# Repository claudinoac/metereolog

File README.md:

# 🌦️ Metereolog

This project involves the development of weather station and a platform capable of collecting data from various sensors, transmitting them to a central platform, storing them, and making them available through a web interface for visualization and analysis. The architecture is modular and scalable, using modern technologies for each stage of the process.

## 1. Project Overview

The main goal is to create a complete system for weather monitoring. This includes acquiring raw data from sensors, efficiently communicating this data to a central server, persistent storage in a time-series optimized database, and finally, visually and interactively presenting this data to users through a web application. Modularity allows for the easy addition of new sensors or replacement of components without affecting the whole system.

## 2. Project Architecture and Features

The architecture is distributed and based on microservices and asynchronous communication, as shown in the diagram. The main features include:

- **Distributed Data Collection:** Sensors are connected to embedded devices (HELTEC WiFi LoRa v3) that act as the network's "edge".
- **Local Gateways**: One local internet-connected dievice that aggregate data from stations in the region via LoRaWAN and transmit over the internet to the web platform via MQTT. 
- **Asynchronous, Message-Oriented Communication:** The MQTT protocol is used to transmit data from gateways to the message broker (RabbitMQ), ensuring low latency and resilience.
- **Centralized Message Processing:** RabbitMQ acts as a central hub for all sensor messages, enabling routing and processing by other components.
- **Optimized Data Persistence:** PostgreSQL and TimescaleDB provide a robust relational database optimized for time-series data.
- **RESTful API:** Facilitates communication between the frontend and backend, offering access to platform data and functionality.
- **Intuitive User Interface:** A modern, responsive web app allows for visualization and management of station data.
- **Containerization (Docker):** Simplifies deployment, portability, and environment management.
- **Modularity:** Each system component is independent, allowing isolated development and maintenance.

## 3. Modular Project Structure and Technologies Used

### 3.1. Data Acquisition Module (Hardware and Firmware)

- **Sensors:**
  - **DHT-11:** Measures temperature and humidity.
  - **Anemometer:** Measures wind speed.
  - **Wind Direction Sensor:** Measures wind direction.
  - **MQ-6:** Measures petroleum-based gas such as propane and butane

- **Heltec WiFi LoRa 32 v3 (Sensor Bus / Weather Station):**
  - Microcontroller responsible for reading sensor data.
  - Acts as the local station’s “brain”.
  - Transmit sensor data to the Gateway node via LoRaWAN
  - **Technologies:** PlatformIO (C++ SDK), LoRaWAN, WiFi.
  - **Features:**
    - Base libraries for each sensor and peripherals (DHT-11, Anemometer, Wind Direction, WiFi, LoRa, etc.).
    - Structured firmware codebase.
    - Local wifi network to view real-time sensors data.
    - Firmware update via OTA (WiFi).
    - Doesn't depend on internet (data transmission via LoRaWAN).

- **Heltec WiFi LoRa 32 v3 (Gateway):**
  - Microcontroller responsible for receiving data from stations via LoRaWAN
  - Publishes sensor data from stations to the MQTT broker.
  - Firmware update via OTA (WiFi).
  - MQTT integration for data transmission.
  - **Technologies:**: PlatformIO (C++ SDK), LoRaWAN, WiFi.
  - **Features:**
    - Base libraries for peripherals (WiFi, LoRa, etc.)
    - Can route data from multiple stations on LoRaWAN reach.
    - Routes data to MQTT broker based on each station specs (credentials, topics).
    - Structured firmware codebase.
    - Firmware update via OTA (WiFi).

### 3.2. Communication and Messaging Module

- **RabbitMQ + MQTT Plugin:**
  - Central message broker for the system.
  - Receives MQTT messages from ESP-32.
  - Forwards them to subscribed components.
  - **Features:**
    - Reliable message delivery.
    - Decoupling producers and consumers.
    - Scalability.
  - **Topic Notation:**  
    - `<device_uid>/<sensor_uid>` = MQTT topics  
    - `mqtt.*` = wildcard listener  
    - `sensors (amqp)` = AMQP forwarding

### 3.3. Data Processing and Persistence Module

- **Message Hub:**
  - Consumes messages from RabbitMQ (`sensors (amqp)`).
  - Validates, transforms, enriches, and stores data.
  - **Technology:** Django (Python).
  - **Features:**
    - Sensor data processing logic.
    - Integration with PostgreSQL + TimescaleDB.

- **PostgreSQL + TimescaleDB:**
  - **PostgreSQL:** Stores users, devices, sensors, roles, permissions, dashboards.
  - **TimescaleDB:** Optimized for time-series sensor readings.
  - **Features:**
    - Efficient data storage (`SensorReading` table).
    - Complex historical query support.
    - System-wide entity management.

### 3.4. Backend Module (API)

- **Django REST API:**
  - Handles communication between frontend and backend.
  - Exposes data and operations through endpoints.
  - **Technology:** Django (Python).
  - **Features:**
    - CRUD endpoints for:
      - Organization (admin only)
      - Role
      - User
      - Device
      - Sensor
      - Dashboards
    - Login endpoint for user authentication.

### 3.5. Frontend Module (User Interface)

- **User Interface (UI):**
  - Web app for interacting with the system.
  - Visualizes sensor data using dashboards.
  - **Technologies:** Vue.js, Quasar, Chart.js.
  - **Features:**
    - Manage Organizations, Users, Devices, Sensors.
    - Create and view custom dashboards.
    - User login.

### 3.6. Web Server Module

- **NGINX:**
  - Reverse proxy for frontend and backend.
  - Serves frontend static files.
  - Manages routing, SSL/TLS, load balancing.
  - **Features:**
    - Optimized content delivery.
    - Unified socket for frontend/backend.
    - Simplified domain/port configuration.

## 4. General Project Features

- **Automated Data Collection:** Continuous readings of temperature, humidity, wind speed/direction, dust/smoke, air quality.
- **Reliable Data Transmission:** MQTT and RabbitMQ ensure delivery.
- **Efficient Time-Series Storage:** TimescaleDB optimized for volume and performance.
- **Entity Management:** Register and manage users, orgs, devices, sensors.
- **Real-Time & Historical Visualization:** Custom dashboards for monitoring.
- **Robust API:** Enables integration and future development.
- **Authentication & Authorization:** Role- and permission-based access.
- **Modularity & Scalability:** Easy to extend sensors, logic, or UI.
- **Simplified Deployment:** Docker streamlines setup and deployment.

## Database Schema

The database schema represents the backend structure for a the web platform, where organizations can manage users, devices, sensors, and dashboards. It is designed with flexibility and scalability in mind, enabling role-based access control, sensor data collection, and customizable dashboards.

At the core of the system is the Organization entity, which acts as a tenant and groups together various resources such as users, devices, and dashboards. Each organization is uniquely identified by a UUID and can be either active or inactive.

Users are associated with a specific organization and can be marked as active or staff (indicating admin-level privileges). Users can have multiple roles, and roles determine their access levels. The Role entity is also organization-specific and connects to a list of Permissions, which define allowed operations on specific resource types, such as sensors or devices.

Devices are the physical units deployed in the field that collect environmental data. Each device belongs to an organization and has unique MQTT credentials for secure communication. Devices can contain multiple sensors, each with a unique identifier. A sensor records specific types of data (e.g., temperature, humidity, gas levels), stores its unit of measurement, and optionally includes configuration such as alert thresholds or additional metadata.

Sensor readings are stored in the SensorReading table, which logs values with timestamps. Each reading is linked to a sensor via its UUID, enabling time-series tracking and analysis of environmental metrics.

To support data visualization and accessibility, the platform includes a Dashboard entity. A dashboard groups together sensors from an organization and provides a human-readable layout to monitor and analyze data. Each dashboard can include multiple sensors and is associated with one organization.

In summary, the system is designed to:

* Support multiple independent organizations.

* Enable fine-grained user permissions through roles and permissions.

* Handle real-time data collection from sensors connected to devices.

* Provide dashboards for data visualization and management.

This schema makes it possible to build a robust, secure, and scalable platform.

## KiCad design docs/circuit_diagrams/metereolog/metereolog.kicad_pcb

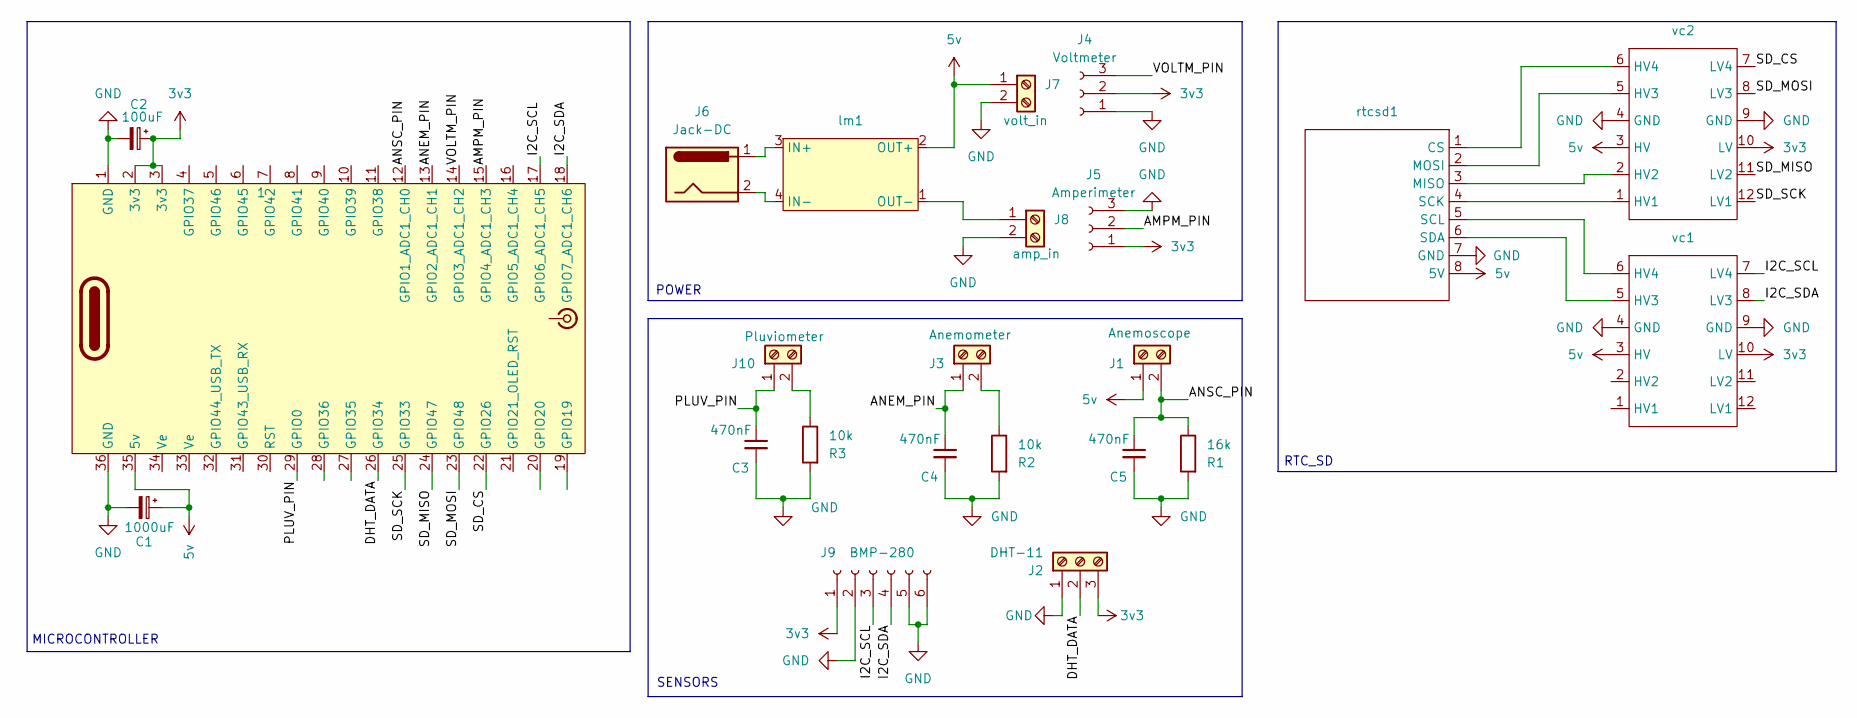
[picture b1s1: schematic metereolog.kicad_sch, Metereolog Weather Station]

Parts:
C1: 1000uF; C_Radial_D10.0mm_H16.0mm_P5.00mm
C2: 100uF; C_Radial_D6.3mm_H11.0mm_P2.50mm
C3, C4, C5: 470nF; C_Rect_L7.0mm_W3.5mm_P5.00mm
HTC1: 1; heltec_wifi_lora_v3
J1: Anemoscope; TerminalBlock_MaiXu_MX126-5.0-02P_1x02_P5.00mm
J2: DHT-11; TerminalBlock_MaiXu_MX126-5.0-03P_1x03_P5.00mm
J3: Anemometer; TerminalBlock_MaiXu_MX126-5.0-02P_1x02_P5.00mm
J4: Voltmeter; PinSocket_1x03_P2.54mm_Vertical
J5: Amperimeter; PinSocket_1x03_P2.54mm_Vertical
J6: Jack-DC; BarrelJack_Horizontal
J7: volt_in; TerminalBlock_MaiXu_MX126-5.0-02P_1x02_P5.00mm
J8: amp_in; TerminalBlock_MaiXu_MX126-5.0-02P_1x02_P5.00mm
J9: BMP-280; PinSocket_1x06_P2.54mm_Vertical
J10: Pluviometer; TerminalBlock_MaiXu_MX126-5.0-02P_1x02_P5.00mm
R1: 16k; R_Axial_DIN0207_L6.3mm_D2.5mm_P7.62mm_Horizontal
R2, R3: 10k; R_Axial_DIN0207_L6.3mm_D2.5mm_P7.62mm_Horizontal
lm1: lm2596_board
rtcsd1: rtc_sdcard
vc1, vc2: logical_converter

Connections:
3v3: C2.1, HTC1.2 (3v3), HTC1.3 (3v3), J2.3, J4.2, J5.1, J9.1, vc1.10 (LV), vc2.10 (LV)
5v: C1.1, HTC1.35 (5v), J1.1, J7.1, lm1.2 (OUT+), rtcsd1.8 (5V), vc1.3 (HV), vc2.3 (HV)
/AMPM_PIN: HTC1.15 (GPIO4_ADC1_CH3), J5.2
/ANEM_PIN: C4.1, HTC1.13 (GPIO2_ADC1_CH1), J3.1
/ANSC_PIN: C5.1, HTC1.12 (GPIO1_ADC1_CH0), J1.2, R1.1
/DHT_DATA: HTC1.26 (GPIO34), J2.2
/I2C_SCL: HTC1.17 (GPIO6_ADC1_CH5), J9.3, vc1.7 (LV4)
/I2C_SDA: HTC1.18 (GPIO7_ADC1_CH6), J9.4, vc1.8 (LV3)
/PLUV_PIN: C3.1, HTC1.29 (GPIO0), J10.1
/SD_CS: HTC1.22 (GPIO26), vc2.7 (LV4)
/SD_MISO: HTC1.24 (GPIO47), vc2.11 (LV2)
/SD_MOSI: HTC1.23 (GPIO48), vc2.8 (LV3)
/SD_SCK: HTC1.25 (GPIO33), vc2.12 (LV1)
/VOLTM_PIN: HTC1.14 (GPIO3_ADC1_CH2), J4.3
GND: C1.2, C2.2, C3.2, C4.2, C5.2, HTC1.1 (GND), HTC1.36 (GND), J2.1, J4.1, J5.3, J7.2, J8.2, J9.2, J9.5, J9.6, R1.2, R2.2, R3.2, rtcsd1.7 (GND), vc1.4 (GND), vc1.9 (GND), vc2.4 (GND), vc2.9 (GND)
unnamed: J3.2, R2.1
unnamed: J8.1, lm1.1 (OUT-)
unnamed: J10.2, R3.1
unnamed: J6.1, lm1.3 (IN+)
unnamed: J6.2, lm1.4 (IN-)
unnamed: rtcsd1.1 (CS), vc2.6 (HV4)
unnamed: rtcsd1.3 (MISO), vc2.2 (HV2)
unnamed: rtcsd1.2 (MOSI), vc2.5 (HV3)
unnamed: rtcsd1.4 (SCK), vc2.1 (HV1)
unnamed: rtcsd1.5 (SCL), vc1.6 (HV4)
unnamed: rtcsd1.6 (SDA), vc1.5 (HV3)

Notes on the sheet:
MICROCONTROLLER
SENSORS
POWER
RTC_SD

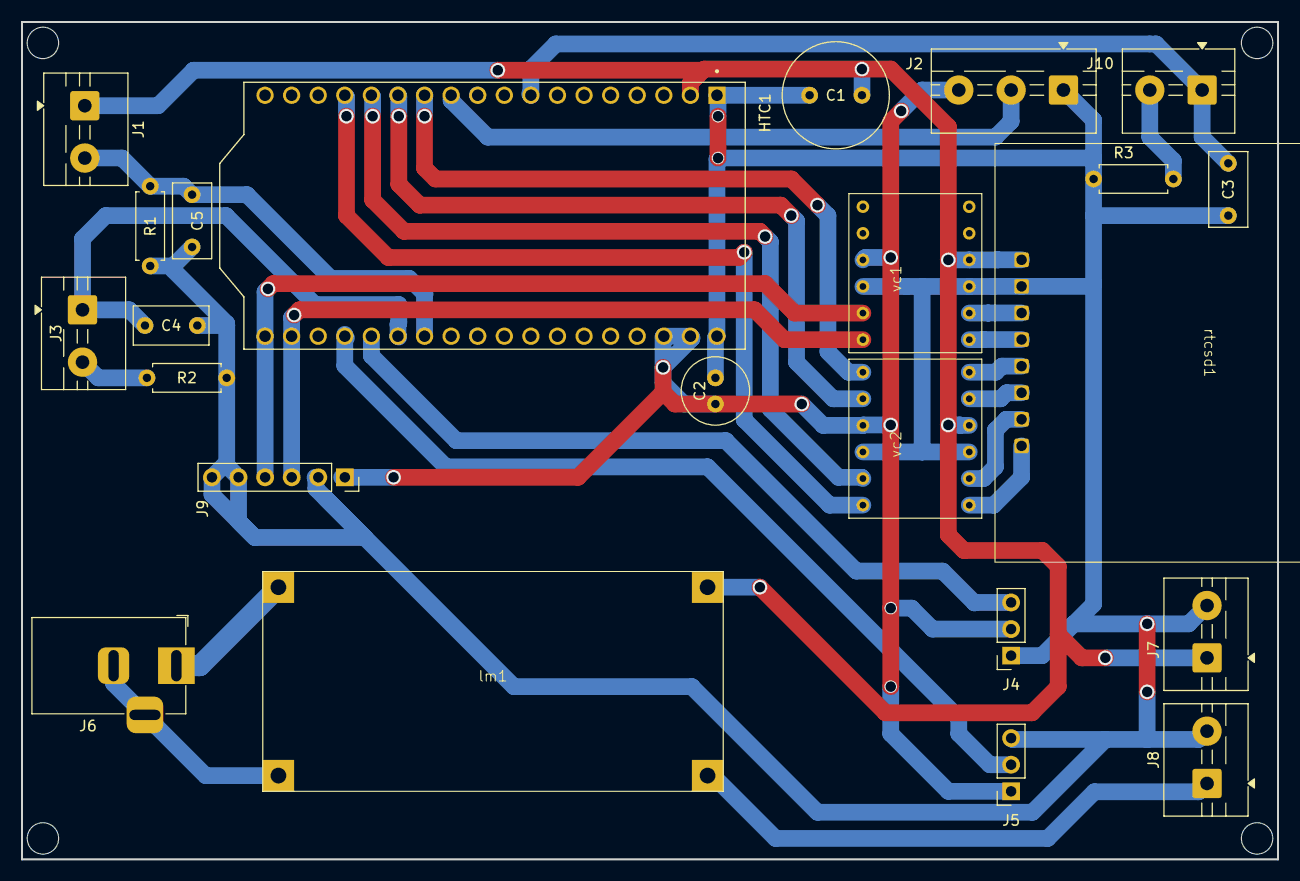
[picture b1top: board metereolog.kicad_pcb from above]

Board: 2 copper layers, 120.0 x 80.0 mm, 23 parts (0 on the bottom side), 26 nets.

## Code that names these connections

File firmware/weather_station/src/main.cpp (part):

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
/*  ==============  I2C Config ================o */

#define I2C_SDA (gpio_num_t) 7
#define I2C_SCL (gpio_num_t) 6

TwoWire *i2c_channel = new TwoWire(1);

/* ============ SDCARD CONFIGS ===================*/ 

#define SD_SCLK 48 // SCK
#define SD_MISO 26 // MISO
#define SD_MOSI 47 // MOSI
#define SD_CS 33 // CS

SPIClass *sd_spi = nullptr; 

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}

void setup_i2c() {
    // pinMode(I2C_SCL, OUTPUT);
    // for (int i = 0; i < 8; i++) {
    //     digitalWrite(I2C_SCL, HIGH);
    //     delayMicroseconds(3);
    //     digitalWrite(I2C_SCL, LOW);
    //     delayMicroseconds(3);
    // }
    // pinMode(I2C_SCL, INPUT_PULLUP);
    // pinMode(I2C_SDA, INPUT_PULLUP);
    if (!i2c_channel->begin(I2C_SDA, I2C_SCL)) {
        Serial.println("Cannot initialize custom bmp I2C Channel");
    };
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// 
//     // 1. Check if SPI bus responds at all (pull CS low, send dummy byte, check MISO)
//     sd_spi->begin(SD_SCLK, SD_MISO, SD_MOSI, SD_CS);
//     pinMode(SD_CS, OUTPUT);
//     digitalWrite(SD_CS, HIGH);
//     delay(100);
// 
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//     }
// 
//     // 5. MISO pin state check
//     pinMode(SD_MISO, INPUT);
//     int misoState = digitalRead(SD_MISO);
//     Serial.printf("\nMISO pin state (idle): %s\n", misoState ? "HIGH (ok)" : "LOW (stuck — bad wiring or short)");
// 
//     // 6. CS pin state check  
//     pinMode(SD_CS, INPUT_PULLUP);
//     delay(10);
//     int csState = digitalRead(SD_CS);
//     Serial.printf("CS pin state: %s\n", csState ? "HIGH (ok)" : "LOW (stuck — check for short)");
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void setup_sdcard() {
    sd_spi = new SPIClass(HSPI);
    sd_spi->begin(SD_SCLK, SD_MISO, SD_MOSI, SD_CS);
    pinMode(SD_CS, OUTPUT);
    digitalWrite(SD_CS, HIGH);
    int countdown = 3;
    while (!SD.begin(SD_CS, *sd_spi, 4000000)) {
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
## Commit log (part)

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2025-04-05 bootstrap: firmware project base
2025-04-11 doc: add architecture overview
2025-04-11 fix: architecture image
2025-04-22 feat: implement backend foundation
2025-04-22 feat: implement foundation for Wifi and MQTT connections
2025-04-25 Implementação de dois sensores
2025-04-25 mudando idioma para ingles
2025-04-25 Criando README para os sensores
2025-04-25 fix: remove specific vscode extension files
2025-04-25 fix: docs & code readability
2025-04-25 fix: calibration of wind direction sensor
2025-04-25 fix: integrate with existing code
2025-04-25 Implementação de dois sensores (#7)
    * Implementação de dois sensores
    * mudando idioma para ingles
    * Criando README para os sensores
    * fix: remove specific vscode extension files
    * fix: docs & code readability
    * fix: calibration of wind direction sensor
2025-04-25 Implementa sensor MQ‑6 e anemômetro - Adiciona drivers em lib/ - Ajusta main.cpp
2025-04-25 Alteraçao documentaçao DHT11
2025-04-25 Alteração na logicado Anemometer
2025-04-25 Documentação DHT11 e Anemometer Altereções no codigo do Anemometer e main
2025-04-25 Documentação basica
2025-04-26 fix: integrate all sensors
2025-04-26 Sensors/mq6 anemometer (#12)
    * Implementa sensor MQ‑6 e anemômetro
    - Adiciona drivers em lib/
    - Ajusta main.cpp
    * Documentação basica
    * Documentação DHT11 e Anemometer
    Altereções no codigo do Anemometer e main
2025-04-28 [ML-12] feat: implement user model
2025-04-28 [ML-19] feat: configure postgres
2025-04-29 [ML-19] feat: configure postgres (#25)
2025-04-29 [ML-12] feat: implement user model (#22)
2025-04-29 [ML-13] feat: implement organization model
2025-04-29 [ML-13] feat: implement organization model (#24)
2025-04-29 [ML-14] feat: create permission model
2025-05-02 [ML-14] feat: create permission model (#26)
2025-05-02 [ML-15] Implement Role Model
2025-05-02 [ML-17] Implement Sensor Model
2025-05-02 [ML-21] feat: Implement Sensor Reading entity and Configure TimescaleDB
2025-05-13 [ML-17] Implement Sensor Model (#30)
    * [ML-15] Implement Role Model
    * [ML-17] Implement Sensor Model
    ---------
2025-05-13 [ML-15] Implement Role Model (#28)
2025-05-13 [MI-11] feat+fix: correct db migrations + add first api endpoint
2025-05-13 fix: mqtt buffer + final payload format
2025-05-13 [MI-20] feat: create foundation code for UI
2025-05-13 fix: fixtures
2025-05-14 docs: add project overview
2025-05-14 docs: add db schema to readme
2025-05-16 fix: relative links for docs images
2025-05-24 [MI-20] refactor: presentation of base views
2025-05-24 [ML-28][ML-34] feat: implement authentication
2025-05-29 [ML-20] feat: implement UI pages and endpoints
    - [ML-34] feat: Login UI page
    - [ML-28] feat: Login API endpoint
    - [ML-31] feat: Devices List UI page
    - [ML-32] feat: Sensor List & Device Dashboard UI Page
    - [ML-25] feat: Device API endpoints: List, Get
    - [ML-26] feat: Sensor API endpoints: List
2025-05-30 docs: update README with detailed project overview
2025-05-30 docs: allow falsy sensor reading values to be stored
2025-05-30 refactor: organize firmware code
2025-06-29 refactor: allow free date selection for sensor dashboard
2025-07-02 [ML-31] feat: implement device creation page
2025-07-02 deployment: configure deployment files
2025-07-02 deployment: create deployment script
2025-07-02 [ML-32] feat: implement sensor create and delete operations
2025-07-02 fix: prod nginx config
2025-07-02 fix: time ranges on charts
2025-07-02 fix: update time scales along with data
2025-07-03 refactor: use metereolog logo in favicon
2025-07-03 [ML-31] refactor: show all device details in dashboard
2025-07-03 [ML-31] refactor: add predefined time filters
2025-07-03 [ML-31] refactor: add more space between device details
2025-07-04 [ML-32] feat: add more ticks on y axis
2025-08-30 feat: add config via env var
2025-11-24 docs: add conceptual, logical diagrams and ddl script
2026-03-25 chore: push static files to vcs
2026-03-25 Create CNAME
2026-04-15 chore: update code to latest version
2026-04-20 chore: update architecture diagram
2026-04-20 docs: update description with LoRa devices
2026-06-19 refactor: split firmware code into gateway and weather station
2026-06-19 feat: circuit diagrams and kicad libs
2026-06-19 feat: add k8s deployment files
2026-06-19 fix: ignore useless files
2026-06-29 Pluviometer: add mutex, debounce, and metrics
    Introduce a mutex to make reed_count access ISR-safe. Add 50ms debounce in the interrupt handler and initialize last_reed in the constructor. Expand PluviometerInfo to include collected_rain_mm and c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
2026-06-29 Fix pluviometer constants
